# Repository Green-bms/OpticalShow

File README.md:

# OpticalShow
OpticalShow is a system that uses optical fibers to transmit the light emitted by an RGB LED matrix.<br>
https://youtu.be/mVdG0zdTeCE?si=2t2tSMmekkIYlkGZ <br>
The system consists of 2 components:
- OpticalShow Mask: that is a resin 3d printed mask into which the 8x8 RGB matrix fits
- OpticalShow Card: the electronic board that contains the microcontroller, with the terminals for the connections

## Examples

The world is mine: https://www.youtube.com/watch?v=pG5Tgg9Z1Hk

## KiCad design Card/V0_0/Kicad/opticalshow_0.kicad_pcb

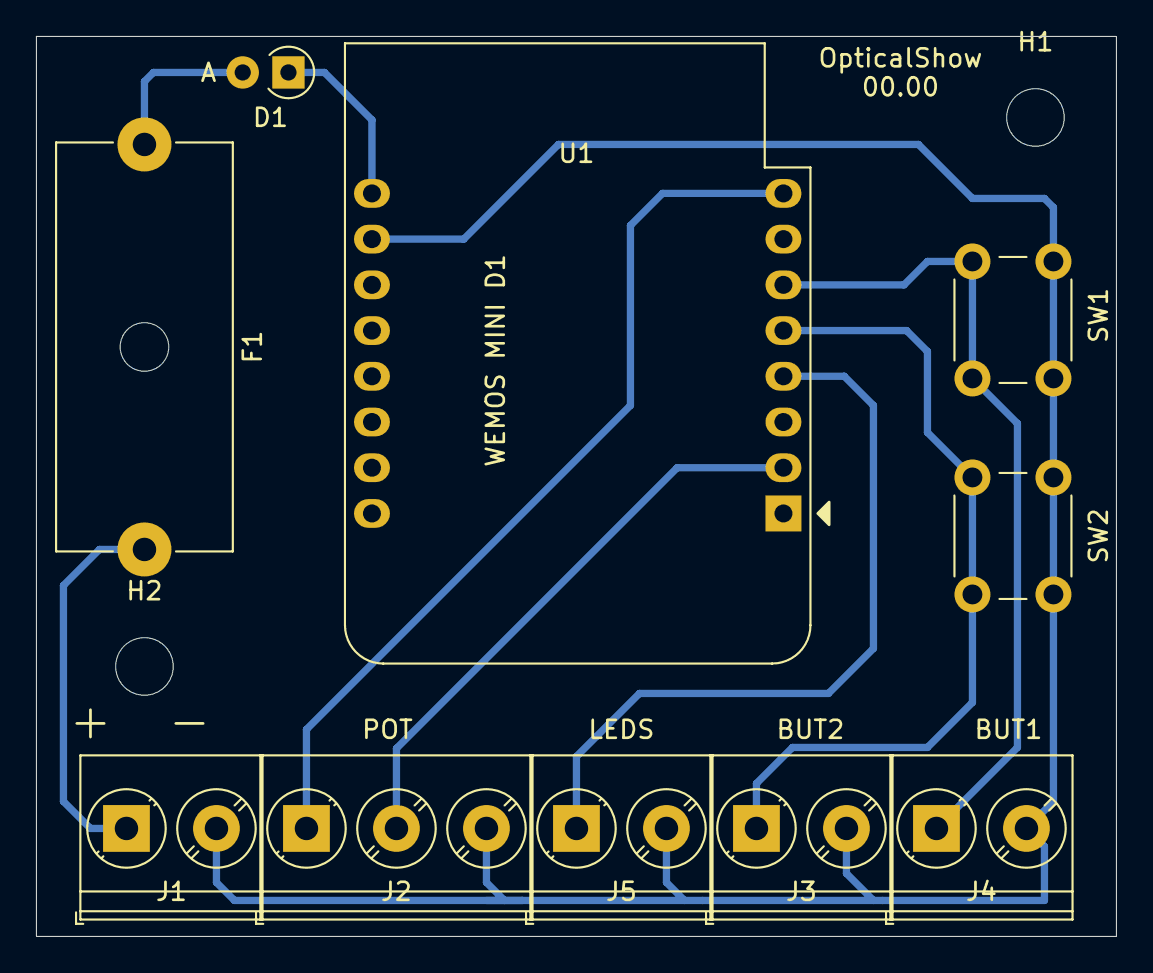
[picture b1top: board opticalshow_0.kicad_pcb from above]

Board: 2 copper layers, 60.0 x 50.0 mm, 12 parts (0 on the bottom side), 9 nets.

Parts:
D1: D; D_A-405_P2.54mm_Vertical_AnodeUp
F1: Fuse 0,5 A; Fuseholder_Cylinder-5x20mm_Schurter_0031_8201_Horizontal_Op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
H1, H2: Hole; MountingHole_3.2mm_M3
J1, J3, J4, J5: Conn_01x02; TerminalBlock_Phoenix_PT-1,5-2-5.0-H_1x02_P5.00mm_Horizontal
J2: Conn_01x03; TerminalBlock_Phoenix_PT-1,5-3-5.0-H_1x03_P5.00mm_Horizontal
SW1, SW2: SW_Push_Dual; SW_PUSH_6mm
U1: WeMos_D1_mini; WEMOS_D1_mini_light

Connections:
+3V3: J2.1, U1.8
GND: J1.2, J2.3, J3.2, J4.2, J5.2, SW1.2, SW2.2, U1.10
unnamed: D1.1, U1.9
unnamed: D1.2, F1.1
unnamed: F1.2, J1.1
unnamed: J2.2, U1.2
unnamed: J3.1, SW2.1, U1.5
unnamed: J4.1, SW1.1, U1.6
unnamed: J5.1, U1.4

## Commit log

2024-02-01 added Youtube video link
